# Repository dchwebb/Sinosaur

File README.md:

# Sinosaur

## Overview

Sinosaur is an LFO and simple envelope generator for use in a Eurorack modular synthesiser. Two envelopes are available: a ramp and a swell, each with a speed and a level control. Each of the sine waves has a rate and level control both of which can be controlled with either envelope.

Sine 1 has a normal output and a phase inverted output. Sines 2 and 3 have a normal output and an FM output, which is derived from the preceding sine wave. Clicking the sine wave's rate or level potentiometer switches the ramp or swell envelopes on for that control. An LED cycles between blue (ramp control), red (swell control) or off to show envelope control.

If a sine's rate is controlled by the ramp, then the rate of the sine wave will increase from its slowest rate up to the rate selected by the potentiometer. In swell mode the rate will increase to the potentiometer level and then fade back to its slowest rate. Envelope control over the sine wave's level works similarly.

A gate input controls the start of the ramp and swell envelopes. The ramp will increase to its selected level whilst the gate is high and then rapidly decrease to zero. The swell rise and fall times are jointly set by the swell potentiometer, with the fall time twice as slow as the rise time.

A clock input is also available to limit the sine wave rates to multiples and divisions of the clock. Changing the rate (either with the potentiometer or envelope) selects from 8x, 4x, 2x, 1, 0.5x and 0.25x the clock rate.

## Outputs

Outputs range from 0V to 6.6V. The level control of the sine waves amplifies from 0v up to a 0V - 6.6V level (ie unipolar rather than bipolar around a central level). The inverted sine's level is 6.6V when the level control is at zero and increases to a maximum swing of 6.6V to 0V.

The levels of the envlopes and sine waves is displayed using LEDs (blue for ramp, orange for swell and white for sine waves).

## Technical

The module is based around an STM32G473 microcontroller, clocked at 170MHz. The various sine wave and envelopes are all generated internally by one of the microcontroller's seven 12 bit DACs.

TL074 quad op-amps are used to amplify (and/or phase invert) the outputs from 3.3V to 6.6V at maximum.

The level LEDs are controlled by PWM by hardware Timer channels on the microcontroller. Clock and Gate inputs are protected with transistor voltage limiters.

The module is designed to support USB input but this is unused at present.

[Components schematic](Hardware/Sinosaur_Components.pdf)

[Controls schematic](Hardware/Sinosaur_Controls.pdf)

## Power

Power is supplied via a 3.3V LDO regulator.

- +12V current draw: 90 mA
- -12V Current draw: 14 mA

## Errata

The inverted output of sine 1 will produce a -6.6V to 0V signal. As detailed on the component schematic a resistor is added to mix in the -12V signal raising the output to 0 - 6.6N.

This is still not ideal as at a zero level the inverted output is at 6.6V. No obvious solution available other than adding an additional DAC.

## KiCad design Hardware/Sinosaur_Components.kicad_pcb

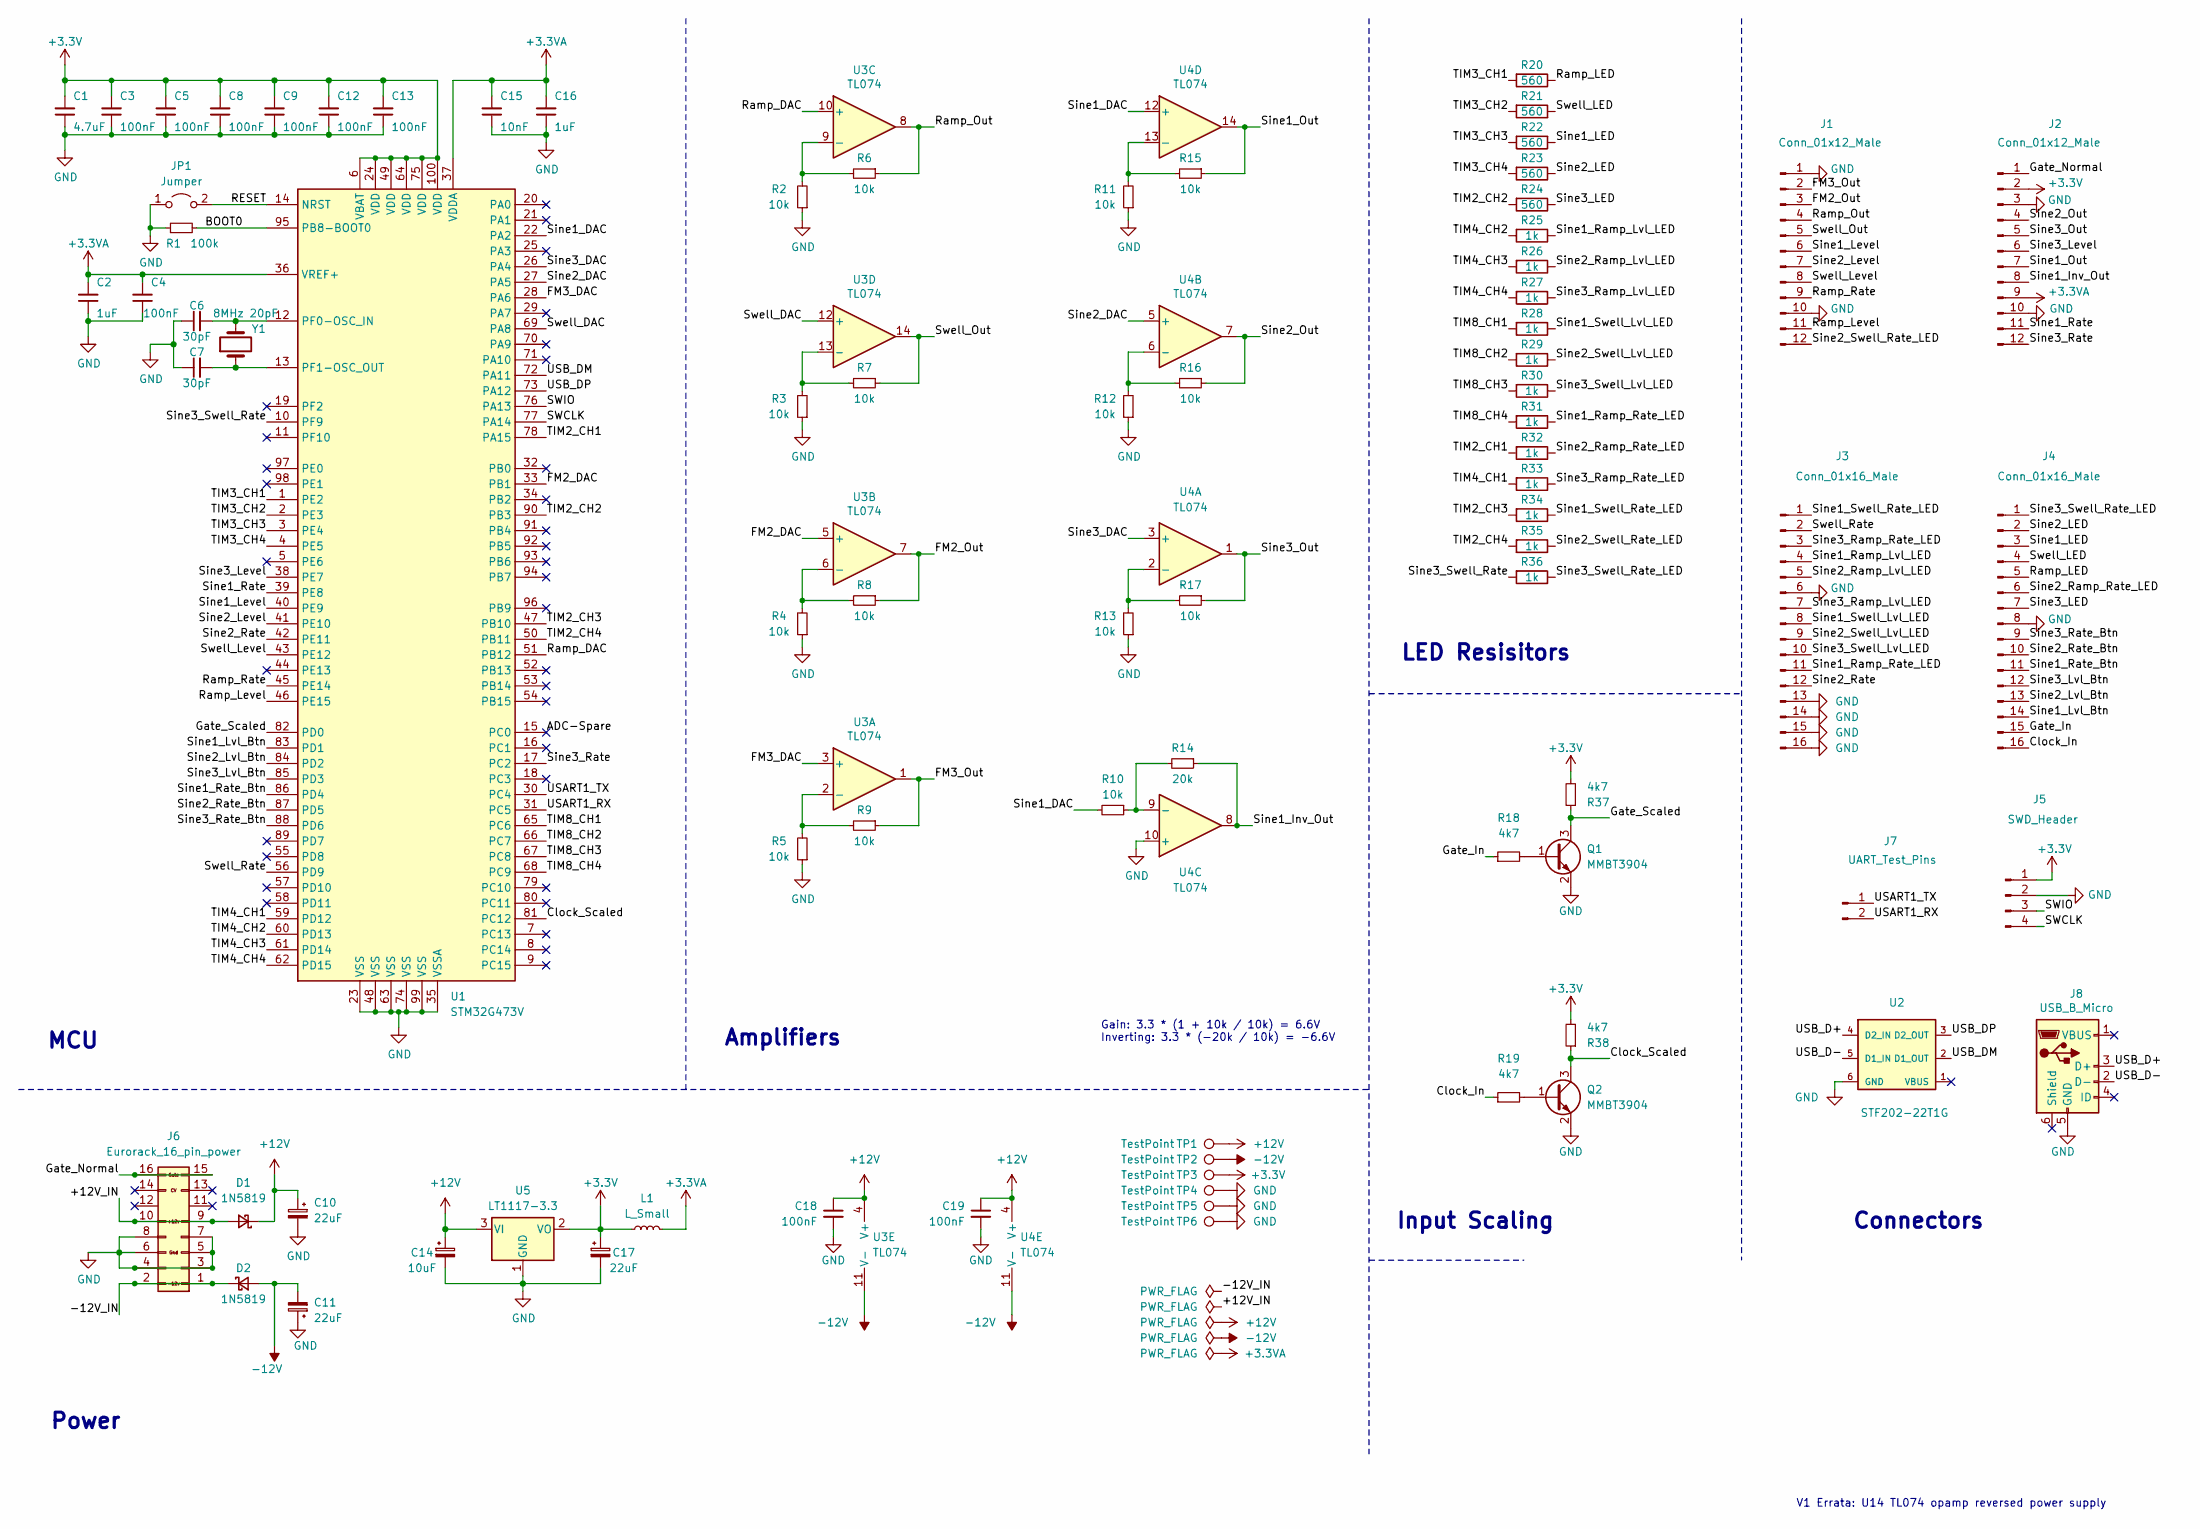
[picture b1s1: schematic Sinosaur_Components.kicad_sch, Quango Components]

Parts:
C1: 4.7uF; C_0603_1608Metric; Part_Number C19666
C2, C16: 1uF; C_0603_1608Metric; Part_Number C15849
C3, C4, C5, C8, C9, C12, C13: 100nF; C_0603_1608Metric; Part_Number C14663
C6, C7: 30pF; C_0603_1608Metric; Part_Number C22397
C10, C11, C17: 22uF; CP_Elec_4x5.8
C14: 10uF; C_1206_3216Metric
C15: 10nF; C_0603_1608Metric; Part_Number C57112
C18, C19: 100nF; C_0603_1608Metric; Part_Number C23630
D1, D2: 1N5819; D_SOD-123
J1, J2: Conn_01x12_Male; PinHeader_1x12_P2.54mm_Vertical
J3, J4: Conn_01x16_Male; PinHeader_1x16_P2.54mm_Vertical
J5: SWD_Header; SWD_header
J6: Eurorack_16_pin_power; Eurorack_16_pin_header
J7: UART_Test_Pins; PinHeader_1x02_P2.54mm_Vertical
J8: USB_B_Micro; USB_Micro-B_Amphenol
JP1: Jumper; SolderJumper-2_P1.3mm_Open_RoundedPad1.0x1.5mm
L1: L_Small; L_0805_2012Metric_Pad1.05x1.20mm_HandSolder; Part_Number C1046
Q1, Q2: MMBT3904; SOT-23; Part_Number C20526
R1: 100k; R_0603_1608Metric; Part_Number C25803
R2, R3, R4, R5, R6, R7, R8, R9, R10, R11, R12, R13, R15, R16, R17: 10k; R_0603_1608Metric
R14: 20k; R_0603_1608Metric
R18, R19, R37, R38: 4k7; R_0603_1608Metric; Part_Number C23162
R20, R21, R22, R23, R24: 560; R_0603_1608Metric; Part_Number C23212
R25, R26, R27, R28, R29, R30, R31, R32, R33, R34, R35, R36: 1k; R_0603_1608Metric; Part_Number C23212
TP1, TP2, TP3, TP4, TP5, TP6: TestPoint; 1mm_Test_Point
U1: STM32G473V; LQFP-100_14x14mm_P0.5mm
U2: STF202-22T1G
U3, U4: TL074; SOIC-14_3.9x8.7mm_P1.27mm
U5: LT1117-3.3; SOT-223-3_TabPin2
Y1: 8MHz 20pF; Crystal_SMD_0603-2Pin_6.0x3.5mm; Part_Number C115962

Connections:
+3.3V: C1.2, C3.2, C5.2, C8.2, C9.2, C12.2, C13.2, C17.1, J2.2, J5.1, L1.1, R37.2, R38.2, TP3.1, U1.6 (VBAT), U1.24 (VDD), U1.49 (VDD), U1.64 (VDD), U1.75 (VDD), U1.100 (VDD), U5.2 (VO)
+3.3VA: C2.2, C4.2, C15.2, C16.2, J2.9, L1.2, U1.36 (VREF+), U1.37 (VDDA)
+12V: C10.1, C14.1, C18.1, C19.1, D1.1 (K), TP1.1, U3.4 (V+), U4.4 (V+), U5.3 (VI)
-12V: C11.2, D2.2 (A), TP2.1, U3.11 (V-), U4.11 (V-)
/+12V_IN: D1.2 (A), J6.9, J6.10
/-12V_IN: D2.1 (K), J6.1, J6.2
/ADC-Spare: U1.15 (PC0)
/BOOT0: R1.2, U1.95 (PB8-BOOT0)
/Clock_In: J4.16, R19.1
/Clock_Scaled: Q2.3 (C), R38.1, U1.81 (PC12)
/FM2_DAC: U1.33 (PB1), U3.5 (+)
/FM2_Out: J1.3, R8.1, U3.7
/FM3_DAC: U1.28 (PA6), U3.3 (+)
/FM3_Out: J1.2, R9.1, U3.1
/Gate_In: J4.15, R18.1
/Gate_Normal: J2.1, J6.15, J6.16
/Gate_Scaled: Q1.3 (C), R37.1, U1.82 (PD0)
/RESET: JP1.2 (B), U1.14 (NRST)
/Ramp_DAC: U1.51 (PB12), U3.10 (+)
/Ramp_LED: J4.5, R20.1
/Ramp_Level: J1.11, U1.46 (PE15)
/Ramp_Out: J1.4, R6.1, U3.8
/Ramp_Rate: J1.9, U1.45 (PE14)
/SWCLK: J5.4, U1.77 (PA14)
/SWIO: J5.3, U1.76 (PA13)
/Sine1_DAC: R10.2, U1.22 (PA2), U4.12 (+)
/Sine1_Inv_Out: J2.8, R14.1, U4.8
/Sine1_LED: J4.3, R22.1
/Sine1_Level: J1.6, U1.40 (PE9)
/Sine1_Lvl_Btn: J4.14, U1.83 (PD1)
/Sine1_Out: J2.7, R15.1, U4.14
/Sine1_Ramp_Lvl_LED: J3.4, R25.1
/Sine1_Ramp_Rate_LED: J3.11, R31.1
/Sine1_Rate: J2.11, U1.39 (PE8)
/Sine1_Rate_Btn: J4.11, U1.86 (PD4)
/Sine1_Swell_Lvl_LED: J3.8, R28.1
/Sine1_Swell_Rate_LED: J3.1, R34.1
/Sine2_DAC: U1.27 (PA5), U4.5 (+)
/Sine2_LED: J4.2, R23.1
/Sine2_Level: J1.7, U1.41 (PE10)
/Sine2_Lvl_Btn: J4.13, U1.84 (PD2)
/Sine2_Out: J2.4, R16.1, U4.7
/Sine2_Ramp_Lvl_LED: J3.5, R26.1
/Sine2_Ramp_Rate_LED: J4.6, R32.1
/Sine2_Rate: J3.12, U1.42 (PE11)
/Sine2_Rate_Btn: J4.10, U1.87 (PD5)
/Sine2_Swell_Lvl_LED: J3.9, R29.1
/Sine2_Swell_Rate_LED: J1.12, R35.1
/Sine3_DAC: U1.26 (PA4), U4.3 (+)
/Sine3_LED: J4.7, R24.1
/Sine3_Level: J2.6, U1.38 (PE7)
/Sine3_Lvl_Btn: J4.12, U1.85 (PD3)
/Sine3_Out: J2.5, R17.1, U4.1
/Sine3_Ramp_Lvl_LED: J3.7, R27.1
/Sine3_Ramp_Rate_LED: J3.3, R33.1
/Sine3_Rate: J2.12, U1.17 (PC2)
/Sine3_Rate_Btn: J4.9, U1.88 (PD6)
/Sine3_Swell_Lvl_LED: J3.10, R30.1
/Sine3_Swell_Rate: R36.2, U1.10 (PF9)
/Sine3_Swell_Rate_LED: J4.1, R36.1
/Swell_DAC: U1.69 (PA8), U3.12 (+)
/Swell_LED: J4.4, R21.1
/Swell_Level: J1.8, U1.43 (PE12)
/Swell_Out: J1.5, R7.1, U3.14
/Swell_Rate: J3.2, U1.56 (PD9)
/TIM2_CH1: R32.2, U1.78 (PA15)
/TIM2_CH2: R24.2, U1.90 (PB3)
/TIM2_CH3: R34.2, U1.47 (PB10)
/TIM2_CH4: R35.2, U1.50 (PB11)
/TIM3_CH1: R20.2, U1.1 (PE2)
/TIM3_CH2: R21.2, U1.2 (PE3)
/TIM3_CH3: R22.2, U1.3 (PE4)
/TIM3_CH4: R23.2, U1.4 (PE5)
/TIM4_CH1: R33.2, U1.59 (PD12)
/TIM4_CH2: R25.2, U1.60 (PD13)
/TIM4_CH3: R26.2, U1.61 (PD14)
/TIM4_CH4: R27.2, U1.62 (PD15)
/TIM8_CH1: R28.2, U1.65 (PC6)
/TIM8_CH2: R29.2, U1.66 (PC7)
/TIM8_CH3: R30.2, U1.67 (PC8)
/TIM8_CH4: R31.2, U1.68 (PC9)
/USART1_RX: J7.2, U1.31 (PC5)
/USART1_TX: J7.1, U1.30 (PC4)
/USB_D+: J8.3 (D+), U2.4 (D2_IN)
/USB_D-: J8.2 (D-), U2.5 (D1_IN)
/USB_DM: U1.72 (PA11), U2.2 (D1_OUT)
/USB_DP: U1.73 (PA12), U2.3 (D2_OUT)
GND: C1.1, C2.1, C3.1, C4.1, C5.1, C6.1, C7.1, C8.1, C9.1, C10.2, C11.1, C12.1, C13.1, C14.2, C15.1, C16.1, C17.2, C18.2, C19.2, J1.1, J1.10, J2.3, J2.10, J3.6, J3.13, J3.14, J3.15, J3.16, J4.8, J5.2, J6.3, J6.4, J6.5, J6.6, J6.7, J6.8, J8.5 (GND), JP1.1 (A), Q1.2 (E), Q2.2 (E), R1.1, R2.1, R3.1, R4.1, R5.1, R11.1, R12.1, R13.1, TP4.1, TP5.1, TP6.1, U1.23 (VSS), U1.35 (VSSA), U1.48 (VSS), U1.63 (VSS), U1.74 (VSS), U1.99 (VSS), U2.6 (GND), U4.10 (+), U5.1 (GND)
unnamed: Q1.1 (B), R18.2
unnamed: Q2.1 (B), R19.2
unnamed: C6.2, U1.12 (PF0-OSC_IN), Y1.2
unnamed: C7.2, U1.13 (PF1-OSC_OUT), Y1.1
unnamed: R5.2, R9.2, U3.2 (-)
unnamed: R4.2, R8.2, U3.6 (-)
unnamed: R2.2, R6.2, U3.9 (-)
unnamed: R3.2, R7.2, U3.13 (-)
unnamed: R13.2, R17.2, U4.2 (-)
unnamed: R12.2, R16.2, U4.6 (-)
unnamed: R10.1, R14.2, U4.9 (-)
unnamed: R11.2, R15.2, U4.13 (-)

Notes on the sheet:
Connectors
Power
V1 Errata: U14 TL074 opamp reversed power supply
MCU
Gain: 3.3 * (1 + 10k / 10k) = 6.6V Inverting: 3.3 * (-20k / 10k) = -6.6V
Input Scaling
Amplifiers
LED Resisitors

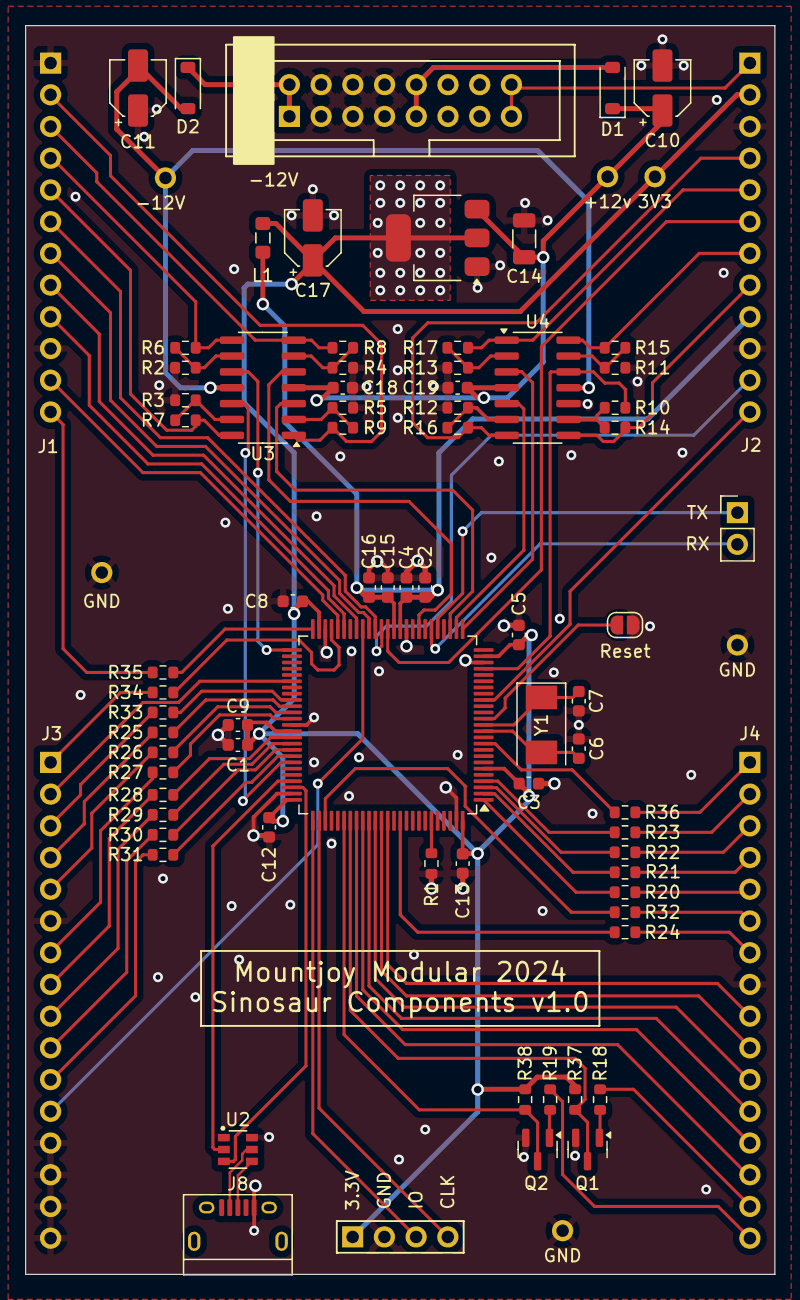
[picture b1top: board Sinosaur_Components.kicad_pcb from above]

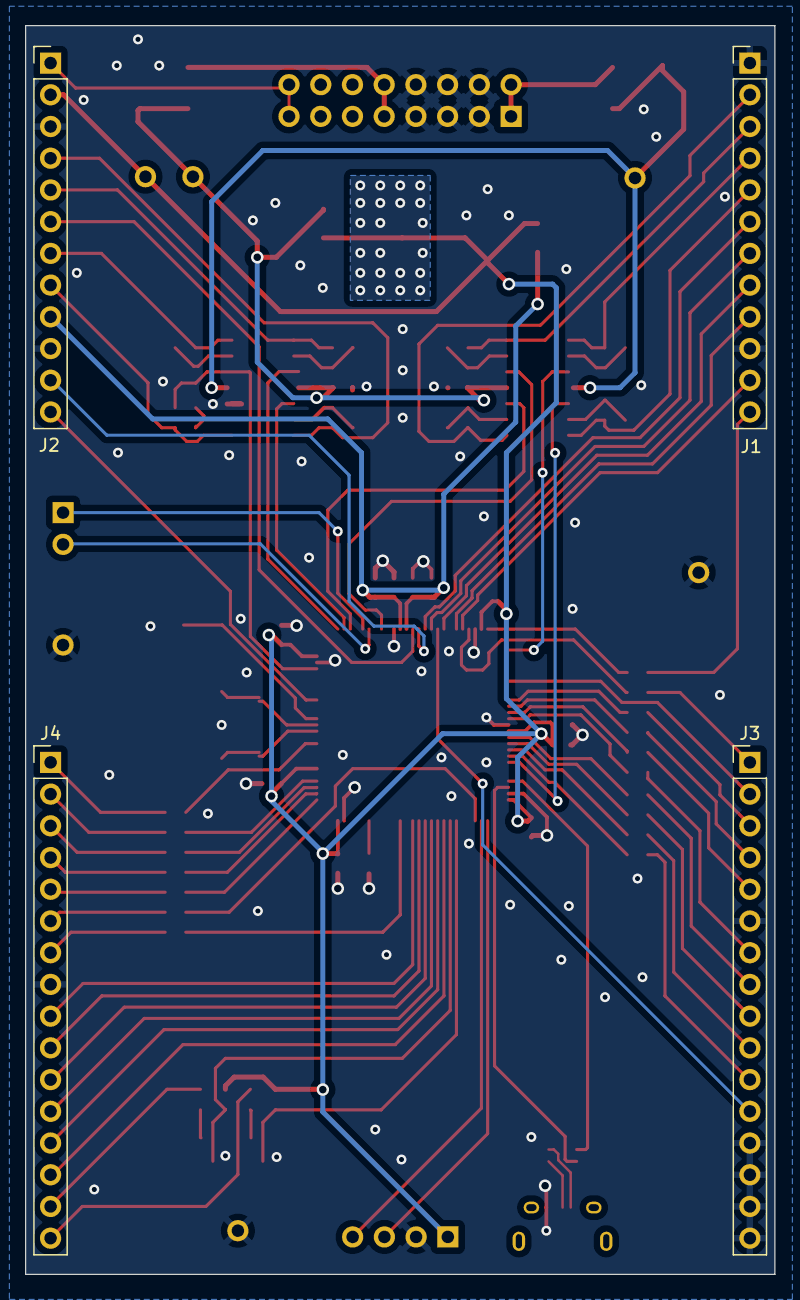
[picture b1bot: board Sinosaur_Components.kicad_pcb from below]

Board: 4 copper layers, 60.0 x 100.0 mm, 83 parts (4 on the bottom side), 99 nets.

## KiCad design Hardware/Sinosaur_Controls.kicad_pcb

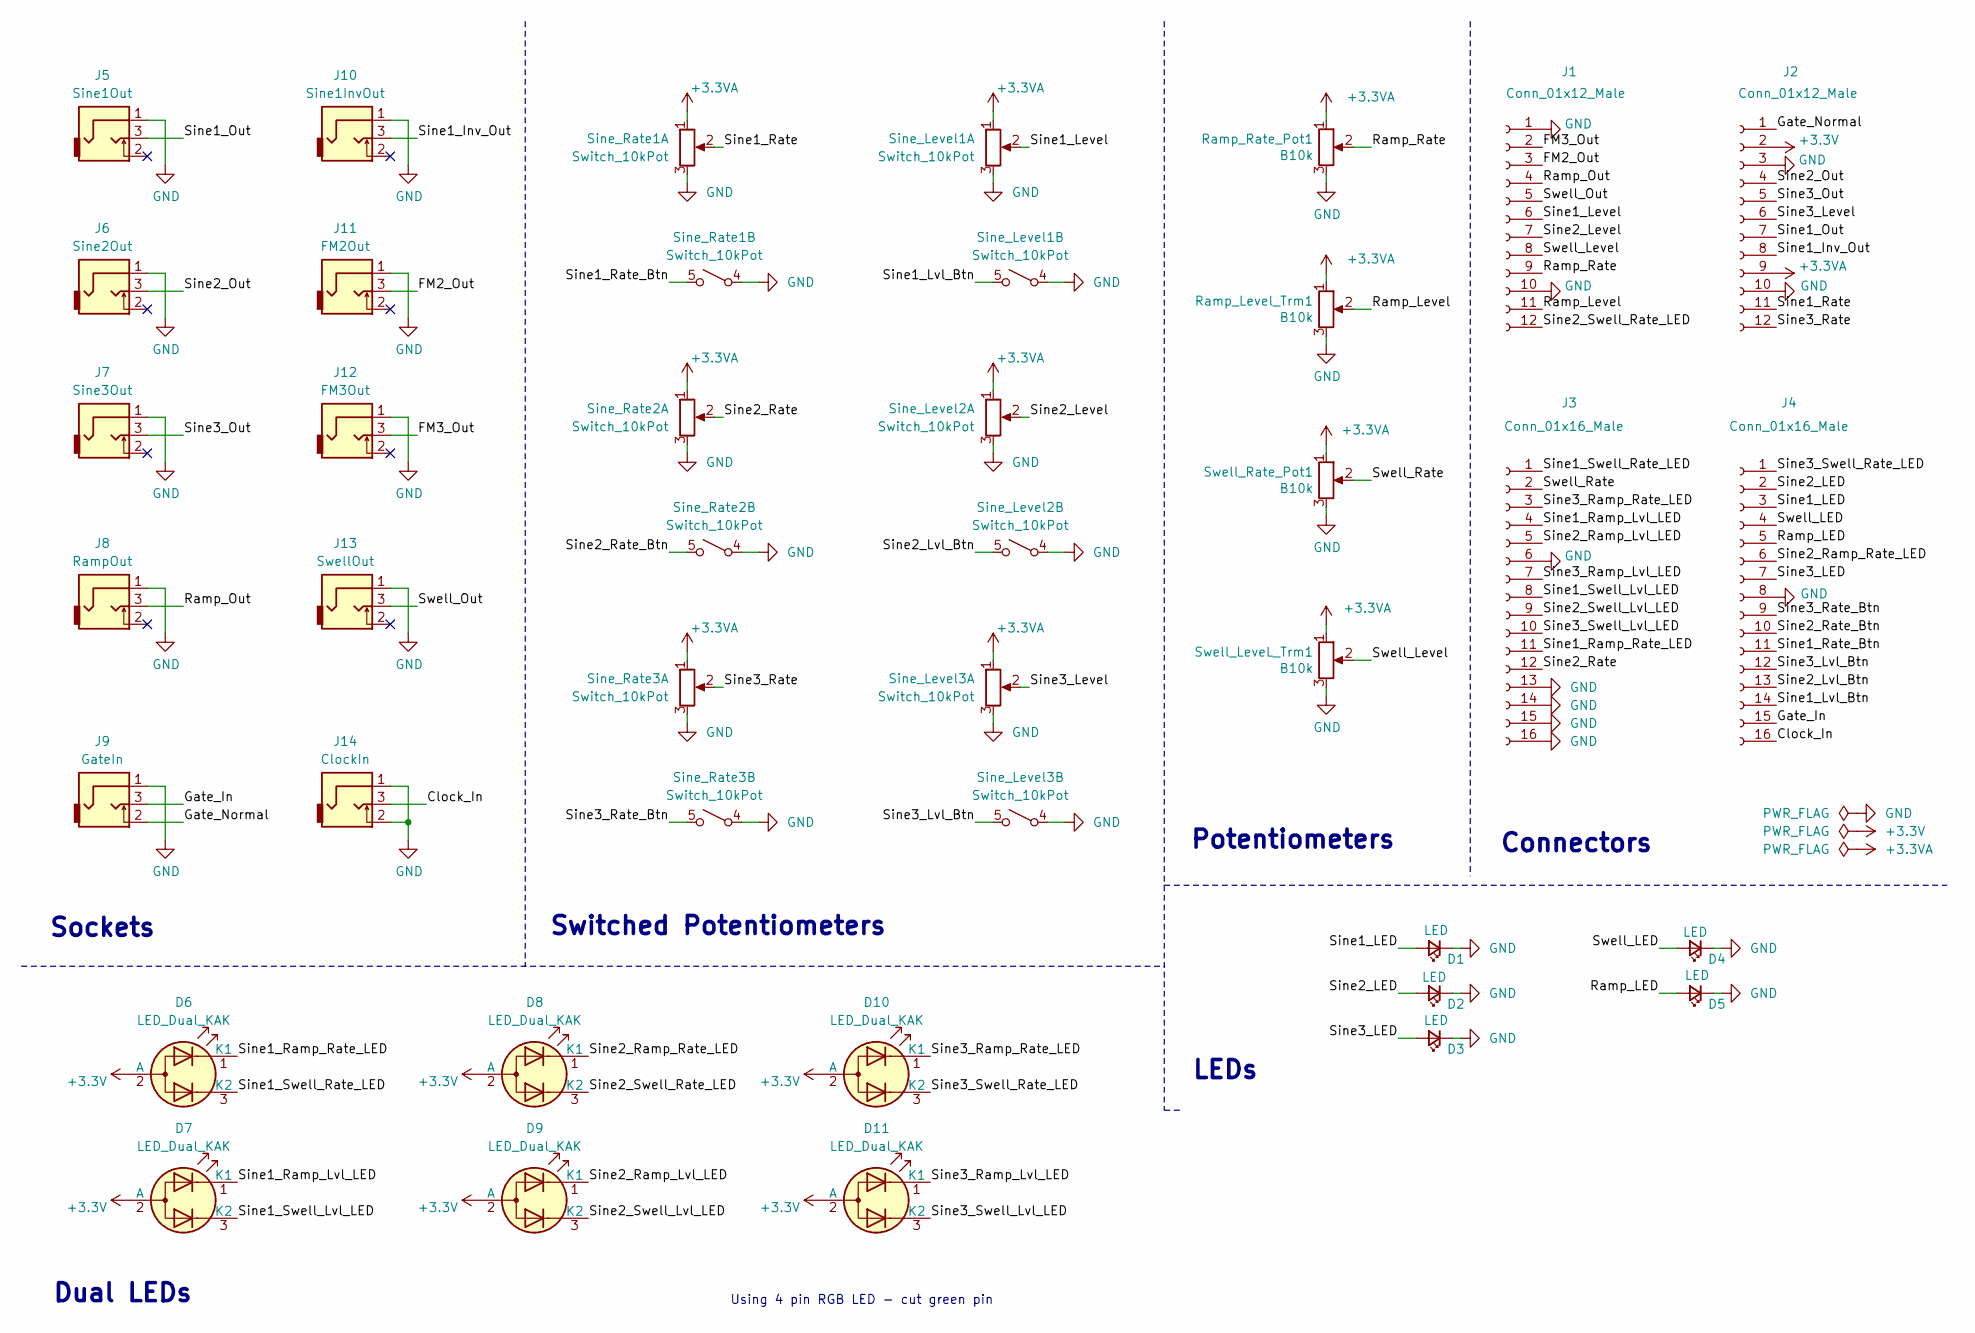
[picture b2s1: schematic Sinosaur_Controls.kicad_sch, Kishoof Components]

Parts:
D1, D2, D3, D4, D5: LED; LED_D3.0mm
D6, D7, D8, D9, D10, D11: LED_Dual_KAK; LED_D3.0mm-3
J1, J2: Conn_01x12_Male; PinSocket_1x12_P2.54mm_Vertical
J3, J4: Conn_01x16_Male; PinSocket_1x16_P2.54mm_Vertical
J5: Sine1Out; THONKICONN_hole
J6: Sine2Out; THONKICONN_hole
J7: Sine3Out; THONKICONN_hole
J8: RampOut; THONKICONN_hole
J9: GateIn; THONKICONN_hole
J10: Sine1InvOut; THONKICONN_hole
J11: FM2Out; THONKICONN_hole
J12: FM3Out; THONKICONN_hole
J13: SwellOut; THONKICONN_hole
J14: ClockIn; THONKICONN_hole
Ramp_Level_Trm1: B10k; Alpha_9mm_Potentiometer_Aligned
Ramp_Rate_Pot1: B10k; Alpha_9mm_Potentiometer_Aligned
Sine_Level1, Sine_Level2, Sine_Level3: Switch_10kPot; Bourns_Switch_Potentiometer
Sine_Rate1, Sine_Rate2, Sine_Rate3: Switch_10kPot; Bourns_Switch_Potentiometer
Swell_LeveL_Trm1: B10k; Alpha_9mm_Potentiometer_Aligned
Swell_Rate_Pot1: B10k; Alpha_9mm_Potentiometer_Aligned

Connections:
+3.3V: D6.2 (A), D7.2 (A), D8.2 (A), D9.2 (A), D10.2 (A), D11.2 (A), J2.2
+3.3VA: J2.9, Ramp_Level_Trm1.1, Ramp_Rate_Pot1.1, Sine_Level1.1, Sine_Level2.1, Sine_Level3.1, Sine_Rate1.1, Sine_Rate2.1, Sine_Rate3.1, Swell_LeveL_Trm1.1, Swell_Rate_Pot1.1
/Clock_In: J4.16, J14.3
/FM2_Out: J1.3, J11.3
/FM3_Out: J1.2, J12.3
/Gate_In: J4.15, J9.3
/Gate_Normal: J2.1, J9.2
/Ramp_LED: D5.2 (A), J4.5
/Ramp_Level: J1.11, Ramp_Level_Trm1.2
/Ramp_Out: J1.4, J8.3
/Ramp_Rate: J1.9, Ramp_Rate_Pot1.2
/Sine1_Inv_Out: J2.8, J10.3
/Sine1_LED: D1.2 (A), J4.3
/Sine1_Level: J1.6, Sine_Level1.2
/Sine1_Lvl_Btn: J4.14, Sine_Level1.5 (2)
/Sine1_Out: J2.7, J5.3
/Sine1_Ramp_Lvl_LED: D7.1 (K1), J3.4
/Sine1_Ramp_Rate_LED: D6.1 (K1), J3.11
/Sine1_Rate: J2.11, Sine_Rate1.2
/Sine1_Rate_Btn: J4.11, Sine_Rate1.5 (2)
/Sine1_Swell_Lvl_LED: D7.3 (K2), J3.8
/Sine1_Swell_Rate_LED: D6.3 (K2), J3.1
/Sine2_LED: D2.2 (A), J4.2
/Sine2_Level: J1.7, Sine_Level2.2
/Sine2_Lvl_Btn: J4.13, Sine_Level2.5 (2)
/Sine2_Out: J2.4, J6.3
/Sine2_Ramp_Lvl_LED: D9.1 (K1), J3.5
/Sine2_Ramp_Rate_LED: D8.1 (K1), J4.6
/Sine2_Rate: J3.12, Sine_Rate2.2
/Sine2_Rate_Btn: J4.10, Sine_Rate2.5 (2)
/Sine2_Swell_Lvl_LED: D9.3 (K2), J3.9
/Sine2_Swell_Rate_LED: D8.3 (K2), J1.12
/Sine3_LED: D3.2 (A), J4.7
/Sine3_Level: J2.6, Sine_Level3.2
/Sine3_Lvl_Btn: J4.12, Sine_Level3.5 (2)
/Sine3_Out: J2.5, J7.3
/Sine3_Ramp_Lvl_LED: D11.1 (K1), J3.7
/Sine3_Ramp_Rate_LED: D10.1 (K1), J3.3
/Sine3_Rate: J2.12, Sine_Rate3.2
/Sine3_Rate_Btn: J4.9, Sine_Rate3.5 (2)
/Sine3_Swell_Lvl_LED: D11.3 (K2), J3.10
/Sine3_Swell_Rate_LED: D10.3 (K2), J4.1
/Swell_LED: D4.2 (A), J4.4
/Swell_Level: J1.8, Swell_LeveL_Trm1.2
/Swell_Out: J1.5, J13.3
/Swell_Rate: J3.2, Swell_Rate_Pot1.2
GND: D1.1 (K), D2.1 (K), D3.1 (K), D4.1 (K), D5.1 (K), J1.1, J1.10, J2.3, J2.10, J3.6, J3.13, J3.14, J3.15, J3.16, J4.8, J5.1, J6.1, J7.1, J8.1, J9.1, J10.1, J11.1, J12.1, J13.1, J14.1, J14.2, Ramp_Level_Trm1.3, Ramp_Rate_Pot1.3, Sine_Level1.3, Sine_Level1.4 (1), Sine_Level2.3, Sine_Level2.4 (1), Sine_Level3.3, Sine_Level3.4 (1), Sine_Rate1.3, Sine_Rate1.4 (1), Sine_Rate2.3, Sine_Rate2.4 (1), Sine_Rate3.3, Sine_Rate3.4 (1), Swell_LeveL_Trm1.3, Swell_Rate_Pot1.3

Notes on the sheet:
Sockets
Dual LEDs
Using 4 pin RGB LED - cut green pin
Connectors
Switched Potentiometers
LEDs
Potentiometers

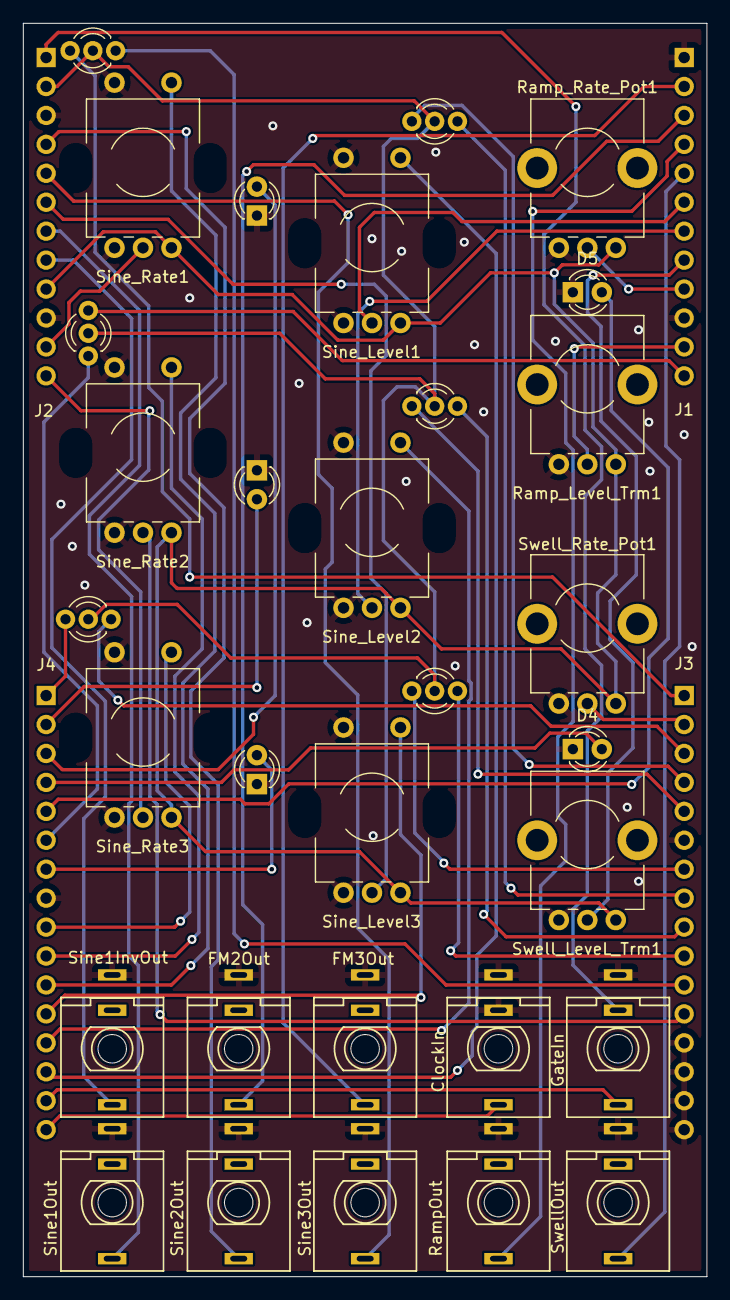
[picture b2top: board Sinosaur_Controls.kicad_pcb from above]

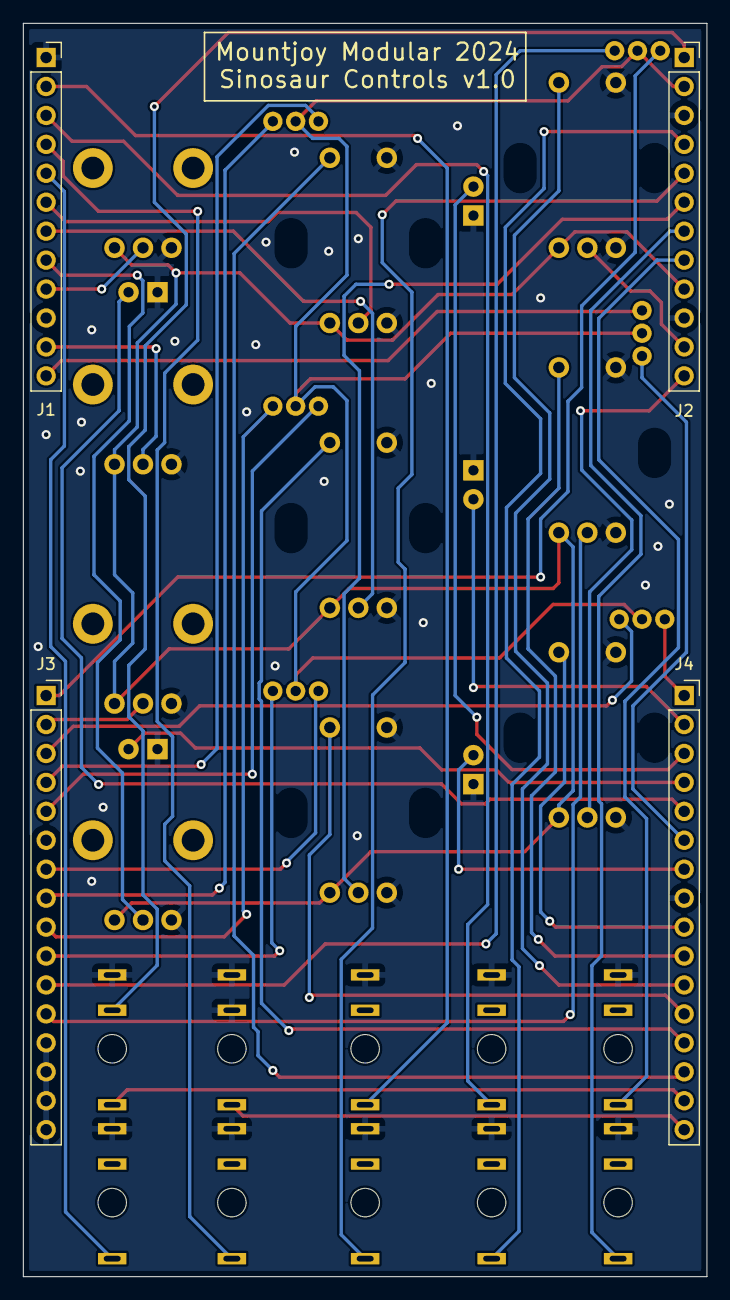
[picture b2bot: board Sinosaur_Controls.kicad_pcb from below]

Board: 2 copper layers, 60.0 x 110.0 mm, 35 parts (4 on the bottom side), 47 nets.

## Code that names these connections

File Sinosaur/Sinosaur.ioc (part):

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Mcu.Name=STM32G473V(B-C-E)Tx
Mcu.Package=LQFP100
Mcu.UserName=STM32G473VCTx
PA11.Mode=Device
PA11.Signal=USB_DM
PA12.Mode=Device
PA12.Signal=USB_DP
PA13.Signal=SYS_JTMS-SWDIO
PA14.Signal=SYS_JTCK-SWCLK
PA15.Signal=S_TIM2_CH1
PA2.Mode=PGA Not Connected-DAC_OUT2-INP
PA2.Signal=OPAMP1_VOUT
PA4.Signal=COMP_DAC11_group
PA5.Signal=COMP_DAC12_group
PA6.Signal=COMP_DAC21_group
PA8.Mode=PGA Not Connected-DAC_OUT2-INP
PA8.Signal=OPAMP5_VOUT
PB1.Mode=PGA Not Connected-DAC_OUT2-INP
PB1.Signal=OPAMP3_VOUT
PB10.Signal=S_TIM2_CH3
PB11.Signal=S_TIM2_CH4
PB12.Mode=PGA Not Connected-DAC_OUT2-INP
PB12.Signal=OPAMP4_VOUT
PB3.Signal=S_TIM2_CH2
PB6.Signal=S_TIM4_CH1
PC12.Signal=GPXTI12
PC2.Mode=IN8-Single-Ended
PC2.Signal=ADC1_IN8
PC4.Mode=Asynchronous
PC4.Signal=USART1_TX
PC5.Mode=Asynchronous
PC5.Signal=USART1_RX
PC6.Signal=S_TIM8_CH1
PC7.Signal=S_TIM8_CH2
PC8.Signal=S_TIM8_CH3
PC9.Signal=S_TIM8_CH4
PD0.Signal=GPXTI0
PD1.Signal=GPXTI1
PD13.Signal=S_TIM4_CH2
PD14.Signal=S_TIM4_CH3
PD15.Signal=S_TIM4_CH4
PD2.Signal=GPXTI2
PD3.Signal=GPXTI3
PD4.Signal=GPXTI4
PD5.Signal=GPXTI5
PD6.Signal=GPXTI6
PD9.Mode=IN13-Single-Ended
PD9.Signal=ADC4_IN13
PE10.Mode=IN14-Single-Ended
PE10.Signal=ADC3_IN14
PE11.Mode=IN15-Single-Ended
PE11.Signal=ADC3_IN15
PE14.Mode=IN1-Single-Ended
PE14.Signal=ADC4_IN1
PE15.Mode=IN2-Single-Ended
PE15.Signal=ADC4_IN2
PE2.Signal=S_TIM3_CH1
PE3.Signal=S_TIM3_CH2
PE4.Signal=S_TIM3_CH3
PE5.Signal=S_TIM3_CH4
PE7.Mode=IN4-Single-Ended
PE7.Signal=ADC3_IN4
PE8.Mode=IN6-Single-Ended
PE8.Signal=ADC3_IN6
PE9.Mode=IN2-Single-Ended
PE9.Signal=ADC3_IN2
PF0-OSC_IN.Mode=HSE-External-Oscillator
PF0-OSC_IN.Signal=RCC_OSC_IN
PF1-OSC_OUT.Mode=HSE-External-Oscillator
PF1-OSC_OUT.Signal=RCC_OSC_OUT
PF9.Signal=GPXTI9
RCC.HSE_VALUE=8000000
RCC.SYSCLKFreq_VALUE=170000000
RCC.SYSCLKSource=RCC_SYSCLKSOURCE_PLLCLK
board=custom

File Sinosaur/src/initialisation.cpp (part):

#include "initialisation.h"

GpioPin debugPin1	{GPIOC, 4, GpioPin::Type::Output};			// PC4: Debug (Marked TX)
GpioPin debugPin2	{GPIOC, 5, GpioPin::Type::Output};			// PC5: Debug (Marked RX)

// 12MHz / 3(M) * 85(N) / 2(R) = 170MHz
#define PLL_M 2
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
void InitDAC()
{
	// Configure 4 DAC outputs PA4 and PA5 are regular DAC1 buffered outputs; PA2 and PB1 are DAC3 via OpAmp1 and OpAmp3 (Manual p.782)

	RCC->AHB2ENR |= RCC_AHB2ENR_GPIOAEN;			// Enable GPIO Clock
	RCC->AHB2ENR |= RCC_AHB2ENR_GPIOBEN;			// Enable GPIO Clock
	RCC->AHB2ENR |= RCC_AHB2ENR_DAC1EN | RCC_AHB2ENR_DAC2EN | RCC_AHB2ENR_DAC3EN | RCC_AHB2ENR_DAC4EN;				// Enable DAC Clock

	DAC1->MCR &= ~DAC_MCR_MODE1_Msk;				// Set to normal mode: DAC1 channel1 is connected to external pin with Buffer enabled
	DAC1->CR |= DAC_CR_EN1;							// Enable DAC using PA4 (DAC_OUT1)

	DAC1->MCR &= ~DAC_MCR_MODE2_Msk;				// Set to normal mode: DAC1 channel2 is connected to external pin with Buffer enabled
	DAC1->CR |= DAC_CR_EN2;							// Enable DAC using PA5 (DAC_OUT2)

	DAC2->MCR &= ~DAC_MCR_MODE1_Msk;				// Set to normal mode: DAC2 channel1 is connected to external pin with Buffer enabled
	DAC2->CR |= DAC_CR_EN1;							// Enable DAC using PA6 (DAC_OUT1)

	// output triggered with DAC->DHR12R1 = x;

	// Opamp for DAC3 Channel 1: Follower configuration mode - output on PA2
	DAC3->MCR |= DAC_MCR_MODE1_0 | DAC_MCR_MODE1_1;	// 011: DAC channel1 is connected to on chip peripherals with Buffer disabled
	DAC3->CR |= DAC_CR_EN1;							// Enable DAC

	OPAMP1->CSR |= OPAMP_CSR_VMSEL;					// 11: Opamp_out connected to OPAMPx_VINM input
	OPAMP1->CSR |= OPAMP_CSR_VPSEL;					// 11: DAC3_CH1  connected to OPAMPx VINP input
	OPAMP1->CSR |= OPAMP_CSR_OPAMPxEN;				// Enable OpAmp: voltage on pin OPAMPx_VINP is buffered to pin OPAMPx_VOUT (PA2)

	// Opamp for DAC3 Channel 2: Follower configuration mode - output on PB1
	DAC3->MCR |= DAC_MCR_MODE2_0 | DAC_MCR_MODE2_1;	// 011: DAC channel2 is connected to on chip peripherals with Buffer disabled
	DAC3->CR |= DAC_CR_EN2;							// Enable DAC

	OPAMP3->CSR |= OPAMP_CSR_VMSEL;					// 11: Opamp_out connected to OPAMPx_VINM input
	OPAMP3->CSR |= OPAMP_CSR_VPSEL;					// 11: DAC3_CH2  connected to OPAMPx VINP input
	OPAMP3->CSR |= OPAMP_CSR_OPAMPxEN;				// Enable OpAmp: voltage on pin OPAMPx_VINP is buffered to pin OPAMPx_VOUT (PB1)

	// Opamp for DAC4 Channel 1: Follower configuration mode - output on PB12
	DAC4->MCR |= DAC_MCR_MODE1_0 | DAC_MCR_MODE1_1;	// 011: DAC channel1 is connected to on chip peripherals with Buffer disabled
	DAC4->CR |= DAC_CR_EN1;							// Enable DAC

	OPAMP4->CSR |= OPAMP_CSR_VMSEL;					// 11: Opamp_out connected to OPAMPx_VINM input
	OPAMP4->CSR |= OPAMP_CSR_VPSEL;					// 11: DAC4_CH1  connected to OPAMPx VINP input
	OPAMP4->CSR |= OPAMP_CSR_OPAMPxEN;				// Enable OpAmp: voltage on pin OPAMPx_VINP is buffered to pin OPAMPx_VOUT (PB12)

	// Opamp for DAC4 Channel 2: Follower configuration mode - output on PA8
	DAC4->MCR |= DAC_MCR_MODE2_0 | DAC_MCR_MODE2_1;	// 011: DAC channel2 is connected to on chip peripherals with Buffer disabled
	DAC4->CR |= DAC_CR_EN2;							// Enable DAC

	OPAMP5->CSR |= OPAMP_CSR_VMSEL;					// 11: Opamp_out connected to OPAMPx_VINM input
	OPAMP5->CSR |= OPAMP_CSR_VPSEL;					// 11: DAC4_CH2  connected to OPAMPx VINP input
	OPAMP5->CSR |= OPAMP_CSR_OPAMPxEN;				// Enable OpAmp: voltage on pin OPAMPx_VINP is buffered to pin OPAMPx_VOUT (PA8)

}


void InitPWMTimer()
{
	// TIM3: PE2 - PE5
	RCC->APB1ENR1 |= RCC_APB1ENR1_TIM3EN;

	GpioPin::Init(GPIOE, 2, GpioPin::Type::AlternateFunction, 2);		// Enable channel 1 PWM output pin on PE2
	GpioPin::Init(GPIOE, 3, GpioPin::Type::AlternateFunction, 2);		// Enable channel 2 PWM output pin on PE3
	GpioPin::Init(GPIOE, 4, GpioPin::Type::AlternateFunction, 2);		// Enable channel 3 PWM output pin on PE4
	GpioPin::Init(GPIOE, 5, GpioPin::Type::AlternateFunction, 2);		// Enable channel 4 PWM output pin on PE5

	TIM3->CCMR1 |= TIM_CCMR1_OC1PE;					// Output compare 1 preload enable
	TIM3->CCMR1 |= TIM_CCMR1_OC2PE;					// Output compare 2 preload enable
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	TIM3->CR1 |= TIM_CR1_CEN;						// Enable counter

	//////////////////////////////////////////////////////////////////////////////////////////////////////////////////
	// TIM2: PB3 TIM2_CH2 (AF1)

	RCC->APB1ENR1 |= RCC_APB1ENR1_TIM2EN;

	GpioPin::Init(GPIOB, 3, GpioPin::Type::AlternateFunction, 1);		// Enable channel 2 PWM output pin on PB3

	TIM2->CCMR1 |= TIM_CCMR1_OC2PE;					// Output compare 2 preload enable
	TIM2->CCMR1 |= (TIM_CCMR1_OC2M_1 | TIM_CCMR1_OC2M_2);	// 0110: PWM mode 1 - In upcounting, channel 2 active if TIMx_CNT<TIMx_CCR2
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
/*--------------------------------------------------------------------------------------------
Configure ADC Channels to be converted:
	Sine3_Rate	 PC2	ADC12_IN8	1

	Sine2_Rate	 PE11	ADC345_IN15	3
	Sine1_Level	 PE9	ADC3_IN2	3
	Sine2_Level	 PE10	ADC345_IN14	3
	Sine3_Level	 PE7	ADC3_IN4,	3

	Sine1_Rate	 PE8	ADC345_IN6	4
	Swell_Rate	 PD9	ADC4_IN13	4
	Swell_Level	 PE12	ADC345_IN16	4
	Ramp_Rate	 PE14	ADC4_IN1	4
	Ramp_Level	 PE15	ADC4_IN2	4
*/

void InitADC1(volatile uint16_t* buffer, uint16_t channels)
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
	/*
	Configure ADC Channels to be converted:
	Sine3_Rate: PC2	ADC12_IN8
	*/

	InitAdcPins(ADC1, {8});
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
	/*--------------------------------------------------------------------------------------------
	Configure ADC Channels to be converted:
	Sine2_Rate	 PE11	ADC345_IN15	3
	Sine1_Level	 PE9	ADC3_IN2	3
	Sine2_Level	 PE10	ADC345_IN14	3
	Sine3_Level	 PE7	ADC3_IN4,	3
	*/

	InitAdcPins(ADC3, {15, 2, 14, 4});
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
	/*--------------------------------------------------------------------------------------------
	Configure ADC Channels to be converted:
	Sine1_Rate	 PE8	ADC345_IN6	4
	Swell_Rate	 PD9	ADC4_IN13	4
	Swell_Level	 PE12	ADC345_IN16	4
	Ramp_Rate	 PE14	ADC4_IN1	4
	Ramp_Level	 PE15	ADC4_IN2	4
	*/

	InitAdcPins(ADC4, {6, 13, 16, 1, 2});
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
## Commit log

2024-06-08 Started Panel Layout
2024-06-09 Reduced Panel Size
2024-06-11 More panel layout
2024-06-12 First draft panel layout
2024-06-13 Started to prepare Component schematic
2024-06-13 Schematic Updates
2024-06-14 Added logo and LEDs to panel
2024-06-14 First draft of schematic
2024-06-14 Started routing components
2024-06-15 Signal Routing done
2024-06-15 Updated file names
2024-06-15 Started laying out control board
2024-06-15 Started control layout
2024-06-16 Control PCB wiring
2024-06-16 Updates to LEDs
2024-06-18 Gerber production
2024-06-18 Gerber production for v1
2024-06-26 Fixed issue with mask on panel pcb
2024-06-26 Started setting up firmware project
2024-06-28 ADCs working
2024-06-28 Hardware working; started adding modulation code
2024-06-29 Started implementing LFOs and envelopes
2024-07-03 Started adding swell and ramp functions
2024-07-04 Implemented rate envelopes
2024-07-04 First pass at FM functionality
2024-07-05 Started adding clocked LFOs
2024-07-06 Clocked LFO with envelope working
2024-07-06 Added config saving for LFO envelope settings
2024-07-07 Tweaking rates; ordered new panels
2024-07-07 Modified envelope scaling and LEDs
2024-07-08 Ramp and swell pots exponentially scaled for better control at low values
2024-07-09 Added REadme; code cleanup
2024-07-17 Added photos
2025-03-24 Typo in readme
